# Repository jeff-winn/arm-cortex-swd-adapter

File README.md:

# ARM Cortex JLink Adapter
This device is intended to serve as an adapter for the Segger JLink (https://www.segger.com/products/debug-probes/j-link) debug probe.

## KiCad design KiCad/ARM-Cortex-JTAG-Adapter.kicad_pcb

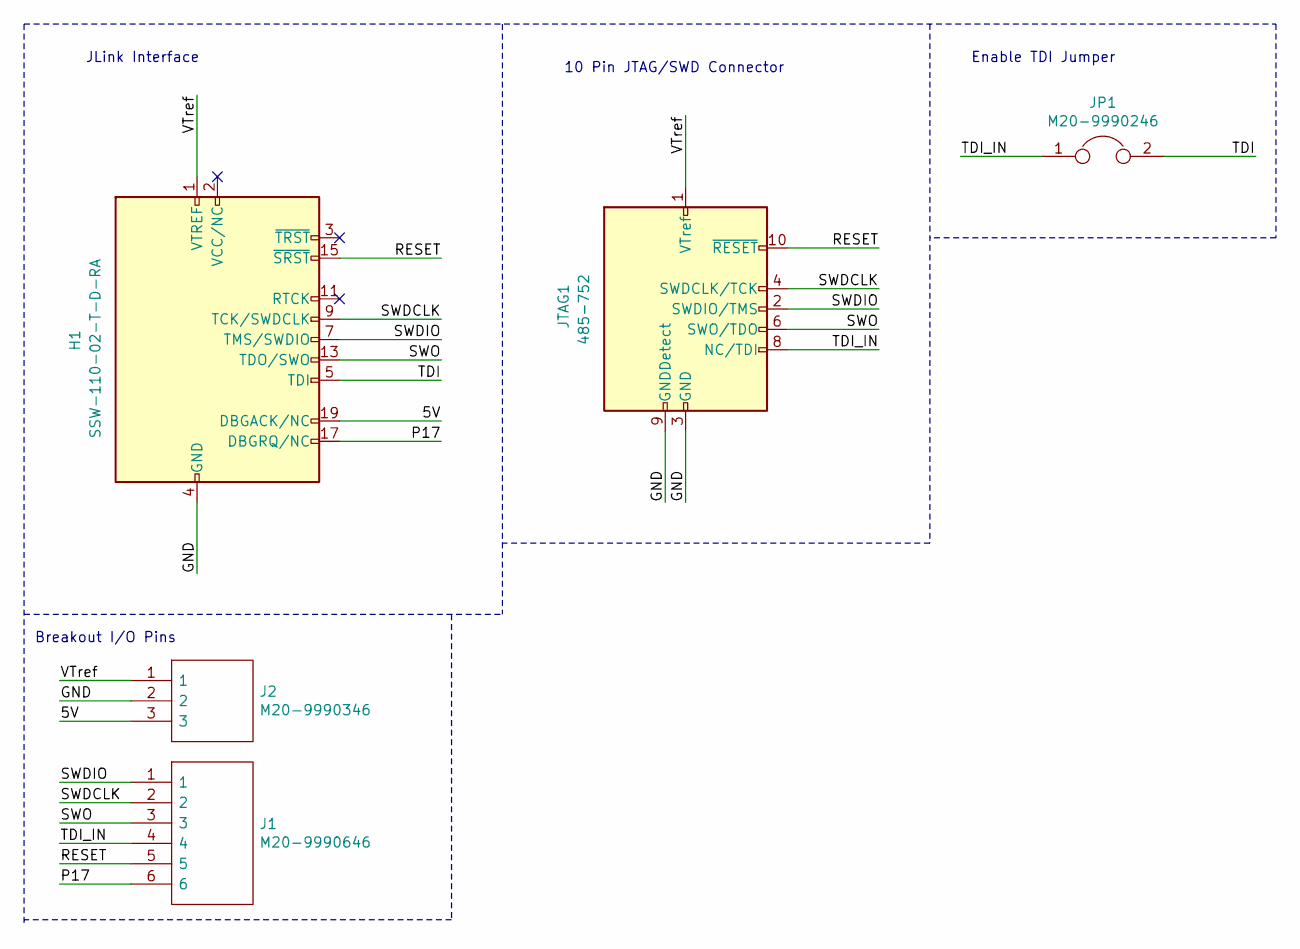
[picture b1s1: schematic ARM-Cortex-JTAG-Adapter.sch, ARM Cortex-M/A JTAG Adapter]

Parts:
H1: SSW-110-02-T-D-RA; IDC-Header_2x10_P2.54mm_Horizontal
J1: M20-9990646; m20-9990646; Mouser Part Number 855-M20-9990646
J2: M20-9990346; m20-9990346; Mouser Part Number 855-M20-9990346
JP1: M20-9990246
JTAG1: 485-752; Adafruit_SWD_Connector_PID_752; MPN 458-752

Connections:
/5V: H1.19 (DBGACK/NC), J2.3
/GND: H1.4 (GND), H1.6 (GND), H1.8 (GND), H1.10 (GND), H1.12 (GND), H1.14 (GND), H1.16 (GND), H1.18 (GND), H1.20 (GND), J2.2, JTAG1.3 (GND), JTAG1.5 (GND), JTAG1.9 (GNDDetect)
/P17: H1.17 (DBGRQ/NC), J1.6
/RESET: H1.15 (~SRST~), J1.5, JTAG1.10 (~RESET~)
/SWDCLK: H1.9 (TCK/SWDCLK), J1.2, JTAG1.4 (SWDCLK/TCK)
/SWDIO: H1.7 (TMS/SWDIO), J1.1, JTAG1.2 (SWDIO/TMS)
/SWO: H1.13 (TDO/SWO), J1.3, JTAG1.6 (SWO/TDO)
/TDI: H1.5 (TDI), JP1.2
/TDI_IN: J1.4, JP1.1, JTAG1.8 (NC/TDI)
/VTref: H1.1 (VTREF), J2.1, JTAG1.1 (VTref)

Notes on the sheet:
Breakout I/O Pins
Enable TDI Jumper
JLink Interface
10 Pin JTAG/SWD Connector

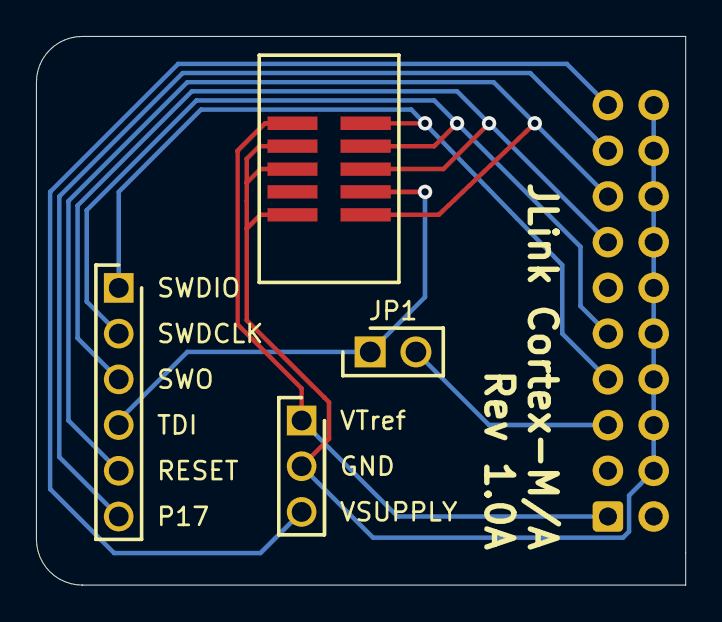
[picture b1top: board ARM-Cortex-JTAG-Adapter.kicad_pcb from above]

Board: 2 copper layers, 36.1 x 30.5 mm, 5 parts (1 on the bottom side), 10 nets.

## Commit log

2020-09-19 Initial check-in.
2020-09-20 Updating schematic and PCB layout.
2020-09-23 Revising schematic for optional TDI pin.
2020-09-25 Adding labels to the TDI connector header.
2020-09-25 Updating README.md
2020-09-29 Replacing connector type for JTAG1.
2020-10-02 Updates.
2020-10-03 Modifying TDI pin route.
2020-10-14 Redoing footprints and symbols.
2020-10-15 Increasing the radius on the corners.
2020-10-15 Updating the version number.
2021-01-17 Flipped the H1 connector layout.
2021-01-18 Adding Adafruit SWD connector module.
2021-01-18 Fixing the schematic version number.
